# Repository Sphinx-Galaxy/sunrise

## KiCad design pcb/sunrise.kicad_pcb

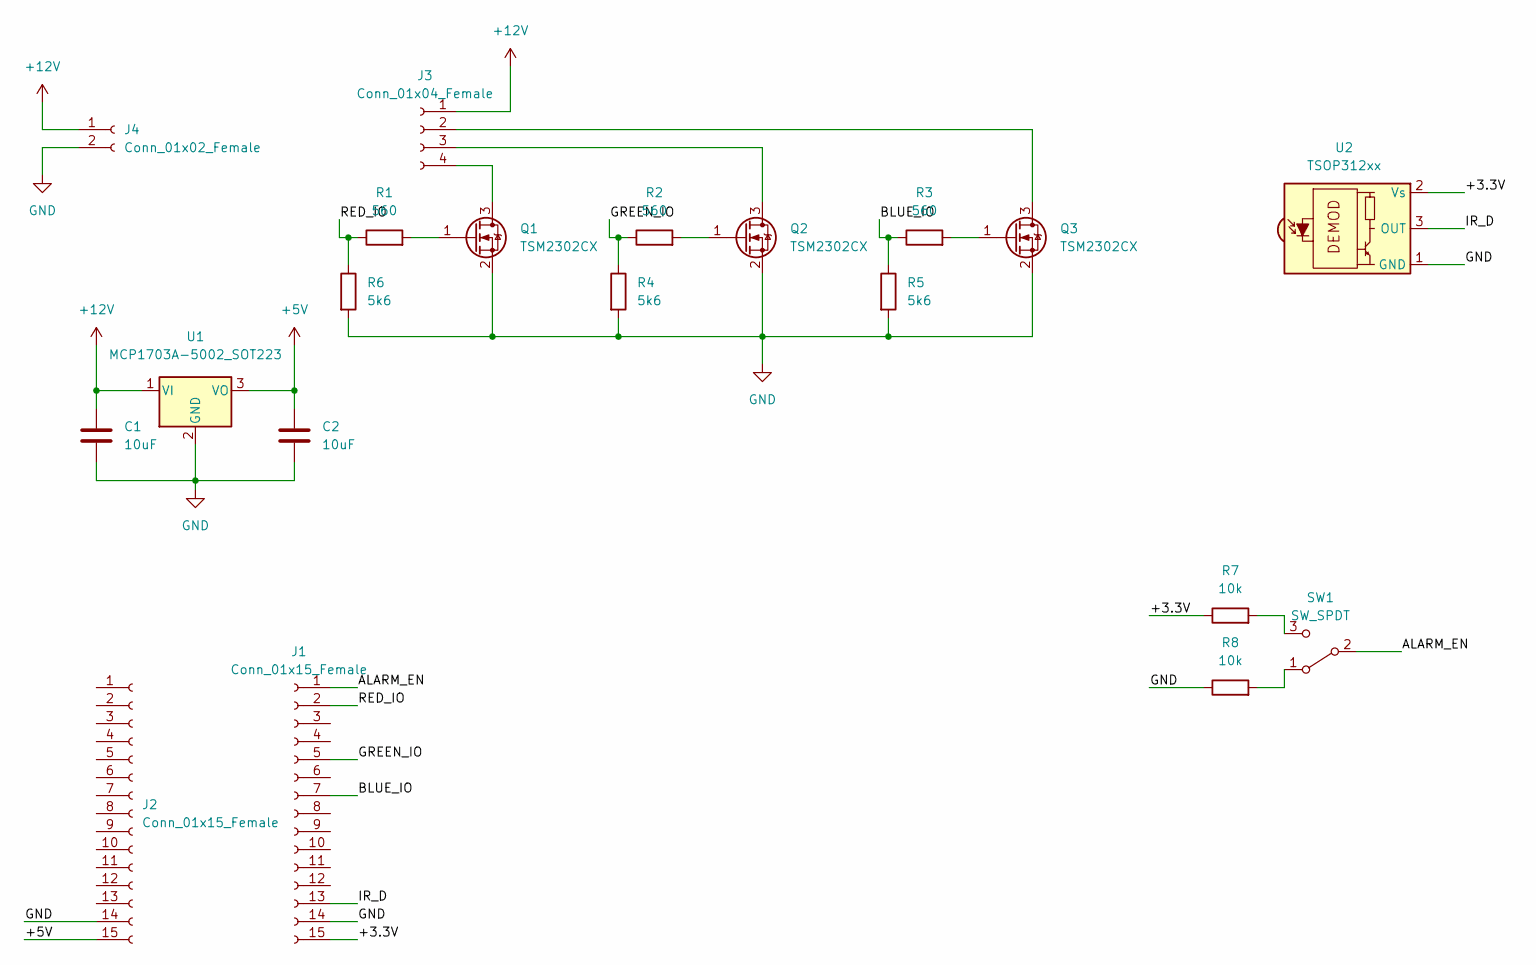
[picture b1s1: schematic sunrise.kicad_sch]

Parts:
C1, C2: 10uF; C_0805_2012Metric
J1, J2: Conn_01x15_Female; PinSocket_1x15_P2.54mm_Vertical
J3: Conn_01x04_Female; PinHeader_1x04_P2.54mm_Vertical
J4: Conn_01x02_Female; PinHeader_1x02_P2.54mm_Vertical
Q1, Q2, Q3: TSM2302CX; SOT-23
R1, R2, R3: 560; R_0805_2012Metric
R4, R5, R6: 5k6; R_0805_2012Metric
R7, R8: 10k; R_0805_2012Metric
SW1: SW_SPDT; SS 13PLP
U1: MCP1703A-5002_SOT223; SOT-223-3_TabPin2
U2: TSOP312xx; Vishay_CAST-3Pin

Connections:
+5V: C2.1, J2.15, U1.3 (VO)
+12V: C1.1, J3.1, J4.1, U1.1 (VI)
/+3.3V: J1.15, R7.1, U2.2 (Vs)
/ALARM_EN: J1.1, SW1.2 (B)
/BLUE_IO: J1.7, R3.1, R5.1
/GREEN_IO: J1.5, R2.1, R4.1
/IR_D: J1.13, U2.3 (OUT)
/RED_IO: J1.2, R1.1, R6.1
GND: C1.2, C2.2, J1.14, J2.14, J4.2, Q1.2 (S), Q2.2 (S), Q3.2 (S), R4.2, R5.2, R6.2, R8.1, U1.2 (GND), U2.1 (GND)
unnamed: J3.2, Q3.3 (D)
unnamed: J3.3, Q2.3 (D)
unnamed: J3.4, Q1.3 (D)
unnamed: Q1.1 (G), R1.2
unnamed: Q2.1 (G), R2.2
unnamed: Q3.1 (G), R3.2
unnamed: R7.2, SW1.3 (C)
unnamed: R8.2, SW1.1 (A)

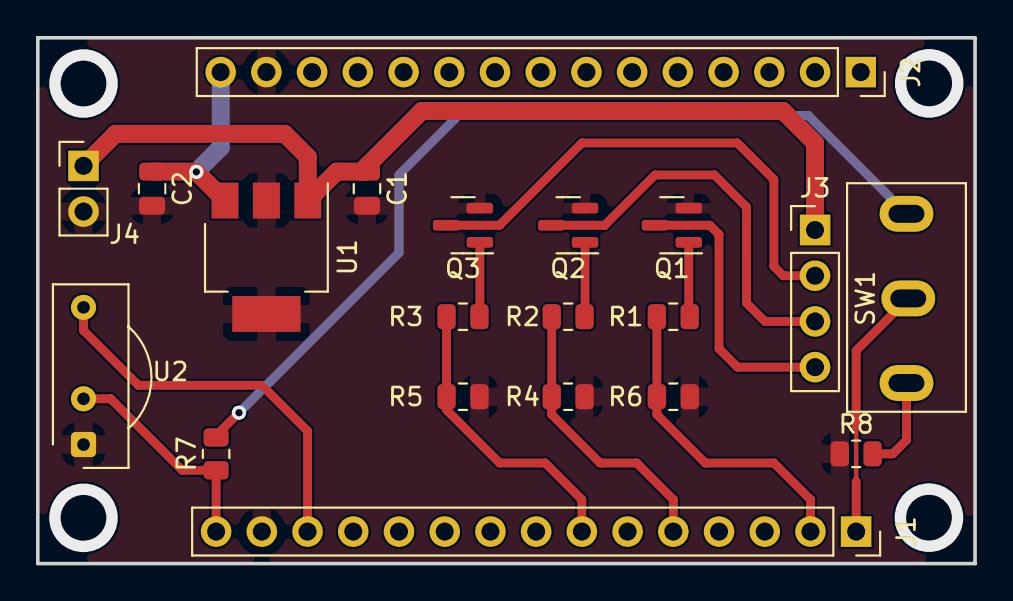
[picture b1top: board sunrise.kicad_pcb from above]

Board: 2 copper layers, 52.1 x 29.2 mm, 20 parts (0 on the bottom side), 17 nets.

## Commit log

2022-08-19 Updated schematic and footprints
2022-08-29 Added resistor
2022-08-29 Added datasheets
2022-09-09 Corrected schematic and finished layout
2022-09-11 Final
2023-01-14 Added IR receiver
2023-01-18 Updated pcb
2023-01-18 Initial code commit
2023-01-20 Final layout
2023-01-20 Added pinout info
2023-01-20 Refactor
2023-01-20 Baseline design
2023-01-21 Corrected component positions
2023-01-22 Added time acquisition
2023-01-22 Removed unnecessary code
2023-01-22 Added wifi
2023-01-22 Changed access style
2023-01-22 Testing functions
2023-01-22 Changed traces
2023-05-04 Continue to program ir and stuff
2023-05-05 Finalize
2023-05-16 Added time
